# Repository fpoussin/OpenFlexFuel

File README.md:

View this project on [CADLAB.io](https://cadlab.io/project/1489). 

# OpenFlexFuel

This is a small project I started to convert my Honda Accord (CH7) to E85.  
The plan is to integrate a small pcb module into the ECU instead of piggybacking wires under the hood.  

There will be a small I2C oled module to monitor duty cycle, fuel ethanol content and possible water contamination.

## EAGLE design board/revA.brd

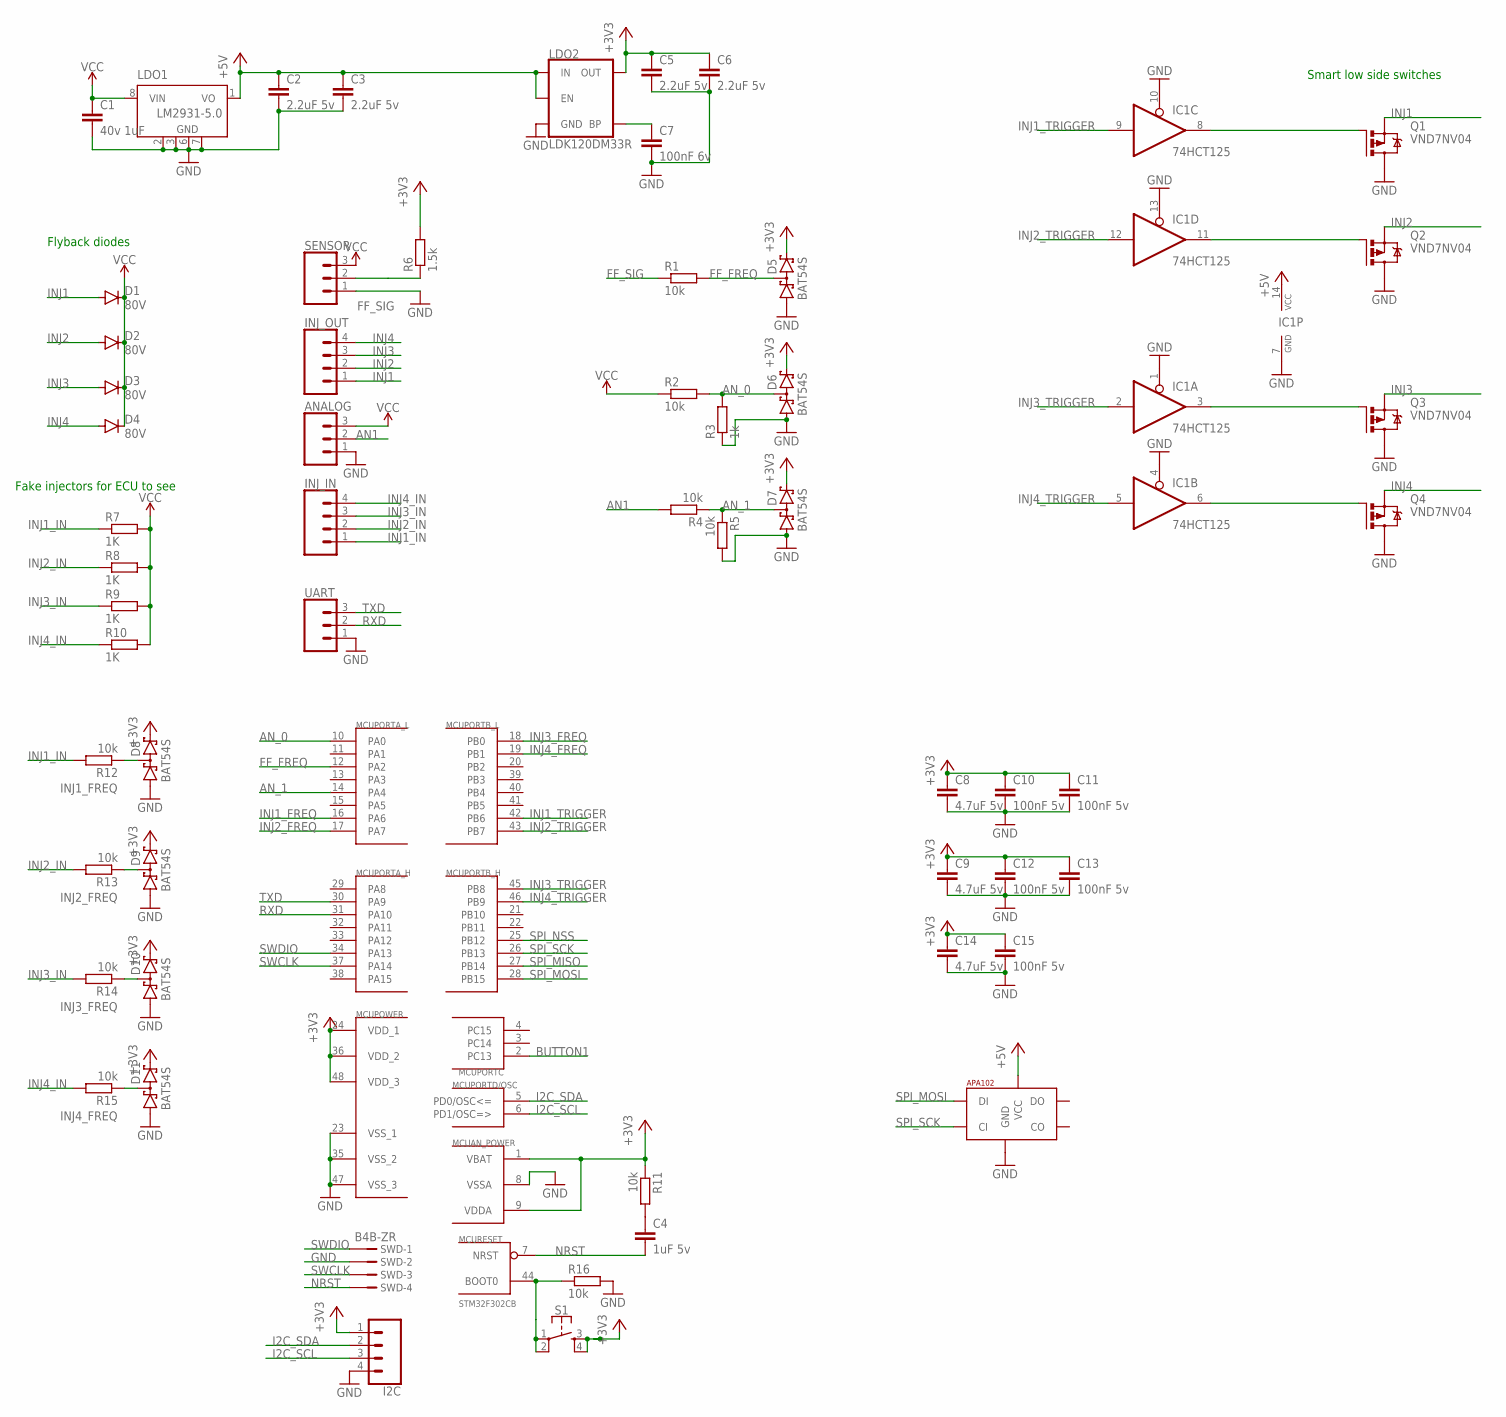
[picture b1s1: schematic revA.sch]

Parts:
ANALOG: CONN_03POLAR_LOCK; MOLEX-1X3_LOCK
C1: 40v 1uF; C0603
C2, C3, C5, C6: 2.2uF 5v; C0603
C4: 1uF 5v; C0603
C7: 100nF 6v; C0603
C8, C9, C14: 4.7uF 5v; C0603
C10, C11, C12, C13, C15: 100nF 5v; C0603
D1, D2, D3, D4: 80V; SMB
D5, D6, D7, D8, D9, D10, D11: BAT54S; SOT23
I2C: CONN_04POLAR_LOCK; MOLEX-1X4_LOCK
IC1: 74HCT125; TSSOP14
INJ_IN: CONN_04POLAR_LOCK; MOLEX-1X4_LOCK
INJ_OUT: CONN_04POLAR_LOCK; MOLEX-1X4_LOCK
LDO1: LM2931-5.0; SO08
LDO2: LDK120DM33R; SOT23-5
LED: APA1025050; APA102_5050
MCU: STM32F302CB; LQFP48_2
Q1, Q2, Q3, Q4: VND7NV04; D-PAK_TO252AA
R1, R2, R4, R5, R11, R12, R13, R14, R15, R16: 10k; R0603
R3: 1k; R0603
R6: 1.5k; R0603
R7, R8, R9, R10: 1K; 0414/15
S1: MOMENTARY-SWITCH-SPST-2-SMD-5.2MM; TACTILE_SWITCH_SMD_5.2MM
SENSOR: CONN_03POLAR_LOCK; MOLEX-1X3_LOCK
SWD: B4B-ZR
UART: CONN_03POLAR_LOCK; MOLEX-1X3_LOCK

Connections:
+3V3: C5.1, C6.1, C8.1, C9.1, C10.1, C11.1, C12.1, C13.1, C14.1, C15.1, D5.2 (C2), D6.2 (C2), D7.2 (C2), D8.2 (C2), D9.2 (C2), D10.2 (C2), D11.2 (C2), I2C.1, LDO2.5 (OUT), MCU.1 (VBAT), MCU.9 (VDDA), MCU.24 (VDD_1), MCU.36 (VDD_2), MCU.48 (VDD_3), R6.2, R11.1, S1.3, S1.4
+5V: C2.1, C3.1, IC1.14 (VCC), LDO1.1 (VO), LDO2.1 (IN), LDO2.3 (EN), LED.1 (VCC)
AN1: ANALOG.2, R4.2
AN_0: D6.3 (C1A2), MCU.10 (PA0), R2.2, R3.2
AN_1: D7.3 (C1A2), MCU.14 (PA4), R4.1, R5.1
BUTTON: MCU.44 (BOOT0), R16.1, S1.1, S1.2
BUTTON1: MCU.2 (PC13)
FF_FREQ: D5.3 (C1A2), MCU.12 (PA2), R1.2
FF_SIG: R1.1, R6.1, SENSOR.2
GND: ANALOG.1, C1.2, C2.2, C3.2, C5.2, C6.2, C7.2, C8.2, C9.2, C10.2, C11.2, C12.2, C13.2, C14.2, C15.2, D5.1 (A1), D6.1 (A1), D7.1 (A1), D8.1 (A1), D9.1 (A1), D10.1 (A1), D11.1 (A1), I2C.4, IC1.1 (OE), IC1.4 (OE), IC1.7 (GND), IC1.10 (OE), IC1.13 (OE), LDO1.2 (GND), LDO1.3 (GND), LDO1.6 (GND), LDO1.7 (GND), LDO2.2 (GND), LED.6 (GND), MCU.8 (VSSA), MCU.23 (VSS_1), MCU.35 (VSS_2), MCU.47 (VSS_3), Q1.4 (D), Q2.4 (D), Q3.4 (D), Q4.4 (D), R3.1, R5.2, R16.2, SENSOR.1, SWD.2, UART.1
I2C_SCL: I2C.3, MCU.6 (PD1/OSC=>)
I2C_SDA: I2C.2, MCU.5 (PD0/OSC<=)
INJ1: D1.A, INJ_OUT.1, Q1.3 (S)
INJ1_FREQ: D8.3 (C1A2), MCU.16 (PA6), R12.1
INJ1_IN: INJ_IN.1, R7.1, R12.2
INJ1_TRIGGER: IC1.9 (I), MCU.42 (PB6)
INJ2: D2.A, INJ_OUT.2, Q2.3 (S)
INJ2_FREQ: D9.3 (C1A2), MCU.17 (PA7), R13.1
INJ2_IN: INJ_IN.2, R8.1, R13.2
INJ2_TRIGGER: IC1.12 (I), MCU.43 (PB7)
INJ3: D3.A, INJ_OUT.3, Q3.3 (S)
INJ3_FREQ: D10.3 (C1A2), MCU.18 (PB0), R14.1
INJ3_IN: INJ_IN.3, R9.1, R14.2
INJ3_TRIGGER: IC1.2 (I), MCU.45 (PB8)
INJ4: D4.A, INJ_OUT.4, Q4.3 (S)
INJ4_FREQ: D11.3 (C1A2), MCU.19 (PB1), R15.1
INJ4_IN: INJ_IN.4, R10.1, R15.2
INJ4_TRIGGER: IC1.5 (I), MCU.46 (PB9)
unnamed: C4.1, R11.2
unnamed: C7.1, LDO2.4 (BP)
unnamed: IC1.11 (O), Q2.1 (G)
unnamed: IC1.8 (O), Q1.1 (G)
unnamed: IC1.6 (O), Q4.1 (G)
unnamed: IC1.3 (O), Q3.1 (G)
NRST: C4.2, MCU.7 (NRST), SWD.4
RXD: MCU.31 (PA10), UART.2
SPI_MISO: MCU.27 (PB14)
SPI_MOSI: LED.4 (DI), MCU.28 (PB15)
SPI_NSS: MCU.25 (PB12)
SPI_SCK: LED.5 (CI), MCU.26 (PB13)
SWCLK: MCU.37 (PA14), SWD.3
SWDIO: MCU.34 (PA13), SWD.1
TXD: MCU.30 (PA9), UART.3
VCC: ANALOG.3, C1.1, D1.C, D2.C, D3.C, D4.C, LDO1.8 (VIN), R2.1, R7.2, R8.2, R9.2, R10.2, SENSOR.3

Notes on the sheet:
Flyback diodes
Fake injectors for ECU to see
Smart low side switches

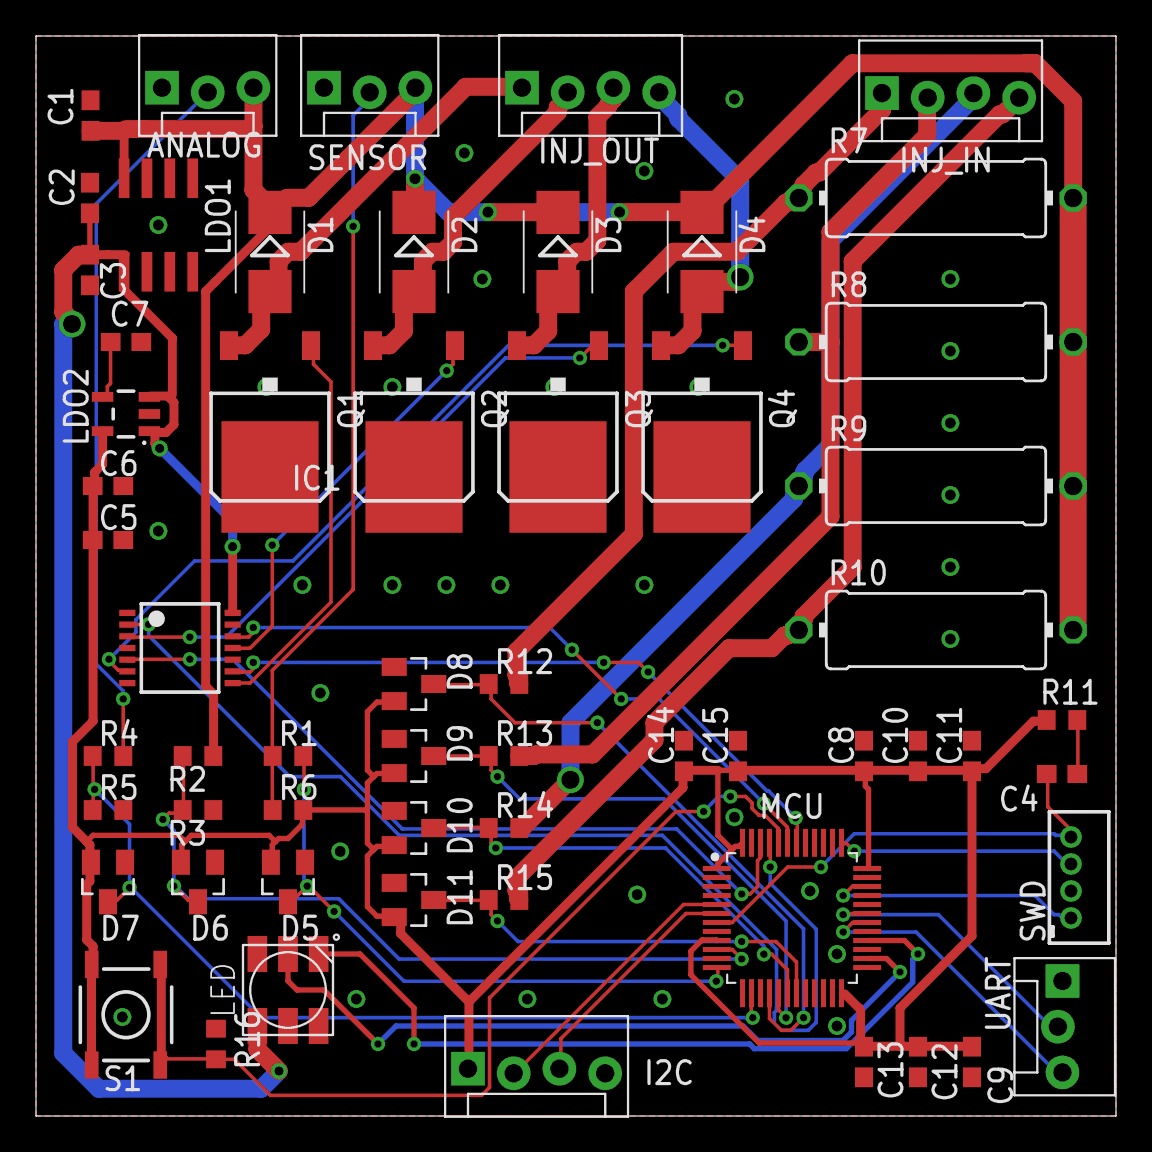
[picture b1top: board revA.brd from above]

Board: 2 copper layers, 60.0 x 60.0 mm, 59 parts (0 on the bottom side), 41 nets.

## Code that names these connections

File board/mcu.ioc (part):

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Mcu.Name=STM32F302C(B-C)Tx
Mcu.Package=LQFP48
Mcu.UserName=STM32F302CBTx
PA0.GPIOParameters=GPIO_Label
PA0.GPIO_Label=AN0
PA0.Mode=IN1-Single-Ended
PA0.Signal=ADC1_IN1
PA10.Mode=Asynchronous
PA10.Signal=USART1_RX
PA13.Mode=Serial_Wire
PA13.Signal=SYS_JTMS-SWDIO
PA14.Mode=Serial_Wire
PA14.Signal=SYS_JTCK-SWCLK
PA2.GPIOParameters=GPIO_Label
PA2.GPIO_Label=FF_FREQ
PA2.Signal=S_TIM15_CH1
PA4.GPIOParameters=GPIO_Label
PA4.GPIO_Label=DAC1
PA4.Signal=COMP_DAC1_group
PA5.GPIOParameters=GPIO_Label
PA5.GPIO_Label=AN1
PA5.Mode=IN2-Single-Ended
PA5.Signal=ADC2_IN2
PA6.GPIOParameters=GPIO_Label
PA6.GPIO_Label=INJ1_IN
PA6.Signal=S_TIM3_CH1
PA7.GPIOParameters=GPIO_Label
PA7.GPIO_Label=INJ2_IN
PA7.Signal=S_TIM3_CH2
PA9.Mode=Asynchronous
PA9.Signal=USART1_TX
PB0.GPIOParameters=GPIO_Label
PB0.GPIO_Label=INJ3_IN
PB0.Signal=S_TIM3_CH3
PB1.GPIOParameters=GPIO_Label
PB1.GPIO_Label=INJ4_IN
PB1.Signal=S_TIM3_CH4
PB6.GPIOParameters=GPIO_Label
PB6.GPIO_Label=INJ1_OUT
PB6.Signal=S_TIM4_CH1
PB7.GPIOParameters=GPIO_Label
PB7.GPIO_Label=INJ2_OUT
PB7.Signal=S_TIM4_CH2
PB8.GPIOParameters=GPIO_Label
PB8.GPIO_Label=INJ3_OUT
PB8.Signal=S_TIM4_CH3
PB9.GPIOParameters=GPIO_Label
PB9.GPIO_Label=INJ4_OUT
PB9.Signal=S_TIM4_CH4
PC13.GPIOParameters=GPIO_Label
PC13.GPIO_Label=BUTTON1
PC13.Signal=GPIO_Input
PF0-OSC_IN.Mode=I2C
PF0-OSC_IN.Signal=I2C2_SDA
PF1-OSC_OUT.Mode=I2C
PF1-OSC_OUT.Signal=I2C2_SCL
RCC.HSEPLLFreq_Value=8000000
RCC.HSE_VALUE=8000000
RCC.SYSCLKFreq_VALUE=8000000
board=custom

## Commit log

2018-11-28 Adding gitignore file
2018-11-28 Updating values
2018-11-29 Some routing, adding mosfets
2018-11-29 Adding buffer for mosfets
2018-11-29 Changing buffer package to TSSOP
2018-11-30 Adding wires, protections, switch
2018-12-02 More routing, adding interfaces
2018-12-03 Routing
2018-12-03 Testing autorouter
2018-12-04 Backlink to CADLAB.io has been added.
2018-12-04 More routing tests
2018-12-04 Adding code and submodules
2018-12-04 Adding code placeholder
2018-12-05 Cleaning routing a bit
2018-12-09 Cleaning routing
2018-12-11 Adding LED
2019-03-11 Added Jenkinsfile
2019-03-11 Updating submodules
2019-03-11 Submodule
2019-03-11 [code] Updated for CH 19.1.x

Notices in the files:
parts and their libraries:
SparkFun-IC-Power: Licensing: Creative Commons ShareAlike 4.0 International - https://creativecommons.org/licenses/by-sa/4.0
